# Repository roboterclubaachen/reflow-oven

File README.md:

# reflow-oven

Description: tbd

## Folder structure

#### `pcbs/pcb_name/`
* KiCad files of the PCBs

#### `code/`
* Main Software contains application for an ILI9341 display running via LVGL on modm for easier user control of the reflow oven.

## License

Software is licensed under [GPLv3](LICENSE).
Hardware (PCB files, ...) is licensed under [CERN OHL v.1.2](LICENSE.hardware).

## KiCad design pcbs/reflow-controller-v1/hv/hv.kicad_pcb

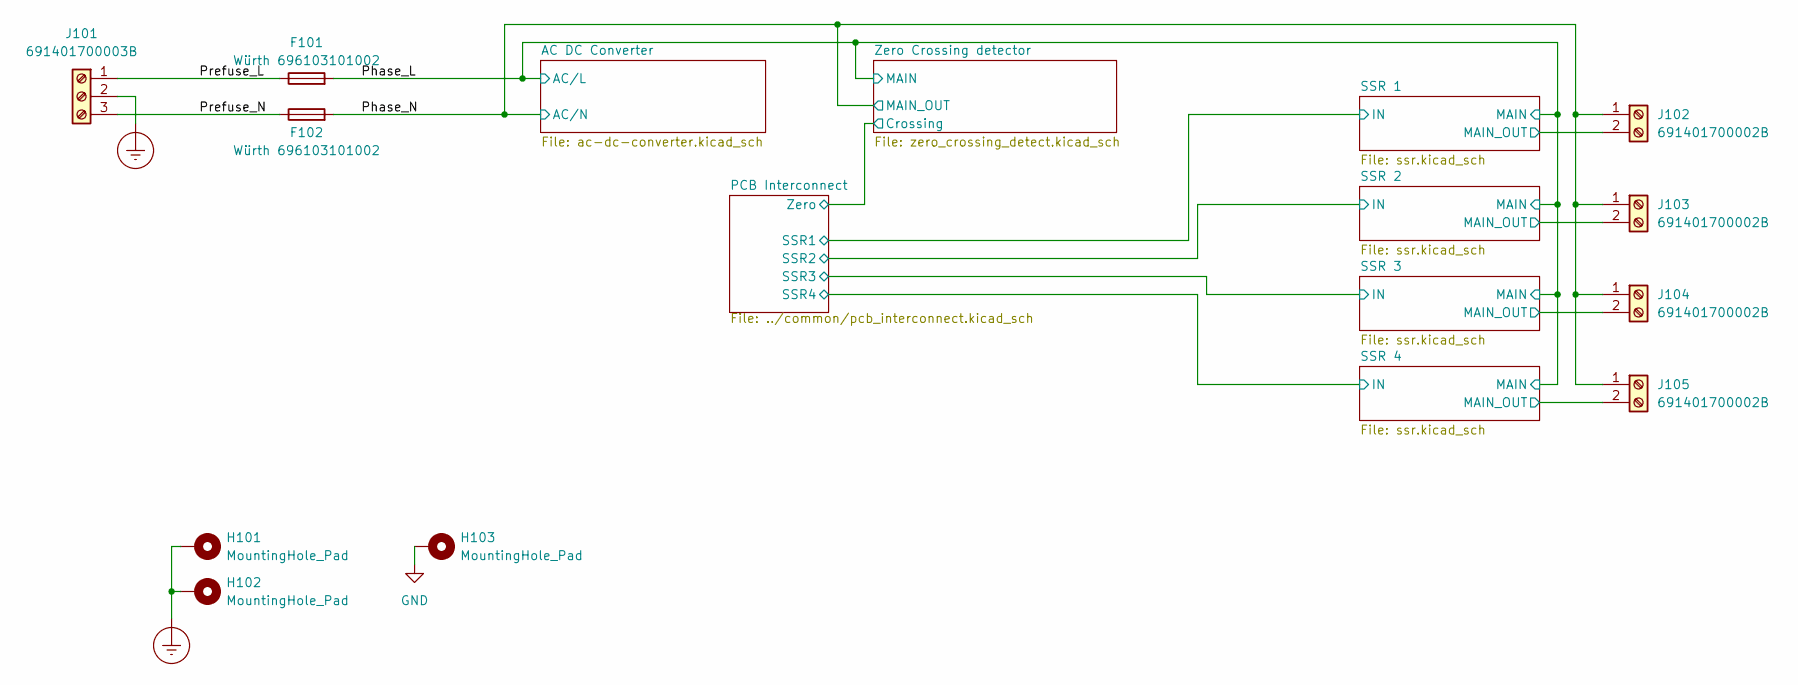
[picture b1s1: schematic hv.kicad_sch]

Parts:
F101, F102: Würth 696103101002; Fuseholder_Cylinder-5x20mm_Wuerth_696103101002-SMD_Horizont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
H101, H102, H103: MountingHole_Pad; Mounting_Wuerth_WA-SMSR-3.2mm_H5.1mm_ReverseMount_9775051960
J101: 691401700003B
J102, J103, J104, J105: 691401700002B

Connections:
/Phase_L: F101.2; also elsewhere on the board
/Phase_N: F102.2, J102.1, J103.1, J104.1, J105.1; also elsewhere on the board
/Prefuse_L: F101.1, J101.1
/Prefuse_N: F102.1, J101.3
/SSR 1/MAIN_OUT: J102.2; also elsewhere on the board
/SSR 2/MAIN_OUT: J103.2; also elsewhere on the board
/SSR 3/MAIN_OUT: J104.2; also elsewhere on the board
/SSR 4/MAIN_OUT: J105.2; also elsewhere on the board
Earth_Protective: H101.1, H102.1, J101.2
GND: H103.1; also elsewhere on the board

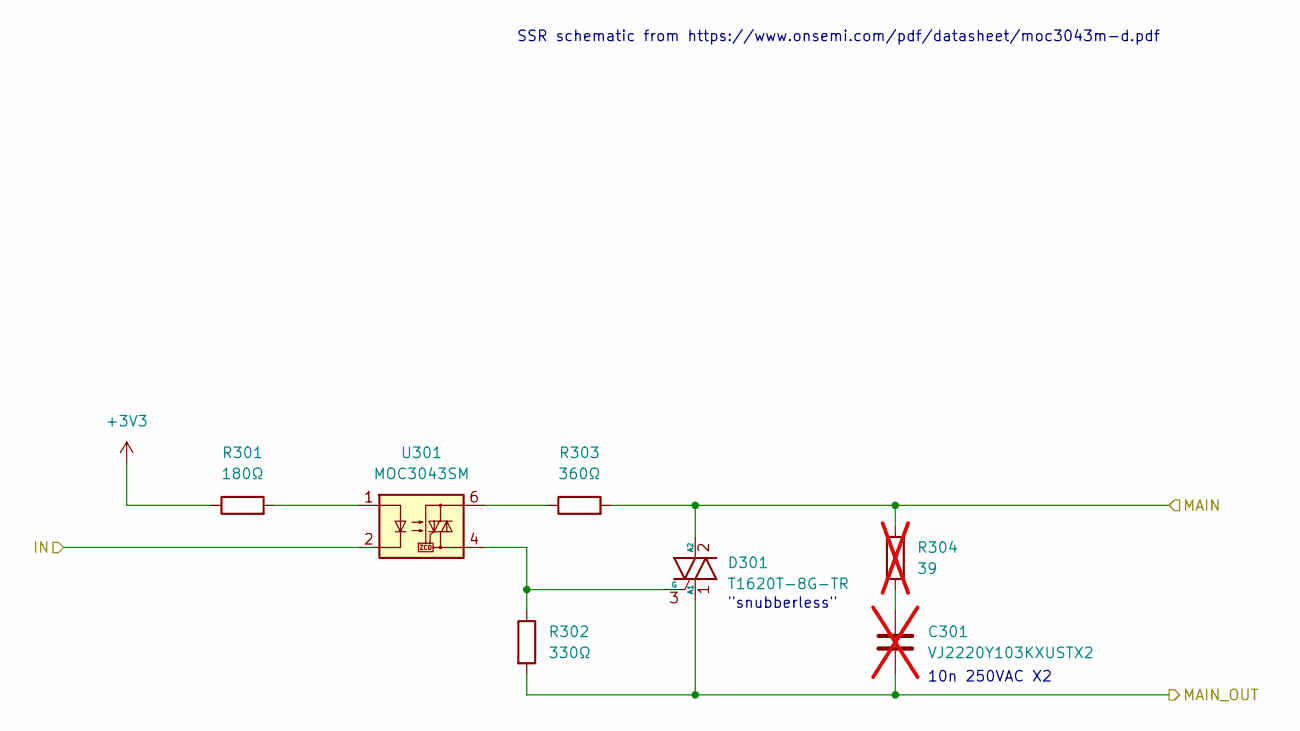
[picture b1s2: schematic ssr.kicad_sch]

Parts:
C301: VJ2220Y103KXUSTX2; C_2220_5750Metric; not fitted
D301: T1620T-8G-TR; TO-263-2
R301: 180Ω; R_0603_1608Metric
R302: 330Ω; R_1206_3216Metric
R303: 360Ω; R_1206_3216Metric
R304: 39; R_1206_3216Metric; not fitted
U301: MOC3043SM; DIP-6_W7.62mm_SMDSocket_SmallPads

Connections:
/PCB Interconnect/SSR1: U301.2; also elsewhere on the board
/Phase_L: D301.2 (A2), R303.2, R304.1; also elsewhere on the board
/SSR 1/MAIN_OUT: C301.2, D301.1 (A1), R302.2; also elsewhere on the board
unnamed: C301.1, R304.2
unnamed: D301.3 (G), R302.1, U301.4
unnamed: R301.2, U301.1
unnamed: R303.1, U301.6

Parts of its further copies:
C401, C501, C601: VJ2220Y103KXUSTX2; C_2220_5750Metric; not fitted
D401, D501, D601: T1620T-8G-TR; TO-263-2
R401, R501, R601: 180Ω; R_0603_1608Metric
R402, R502, R602: 330Ω; R_1206_3216Metric
R403, R503, R603: 360Ω; R_1206_3216Metric
R404, R504, R604: 39; R_1206_3216Metric; not fitted
U401, U501, U601: MOC3043SM; DIP-6_W7.62mm_SMDSocket_SmallPads

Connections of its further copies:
/PCB Interconnect/SSR2: U401.2; also elsewhere on the board
/PCB Interconnect/SSR3: U501.2; also elsewhere on the board
/PCB Interconnect/SSR4: U601.2; also elsewhere on the board
/Phase_L: D401.2 (A2), D501.2 (A2), D601.2 (A2), R403.2, R404.1, R503.2, R504.1, R603.2, R604.1; also elsewhere on the board
/SSR 2/MAIN_OUT: C401.2, D401.1 (A1), R402.2; also elsewhere on the board
/SSR 3/MAIN_OUT: C501.2, D501.1 (A1), R502.2; also elsewhere on the board
/SSR 4/MAIN_OUT: C601.2, D601.1 (A1), R602.2; also elsewhere on the board
unnamed: C401.1, R404.2
unnamed: C501.1, R504.2
unnamed: C601.1, R604.2
unnamed: D401.3 (G), R402.1, U401.4
unnamed: D501.3 (G), R502.1, U501.4
unnamed: D601.3 (G), R602.1, U601.4
unnamed: R401.2, U401.1
unnamed: R403.1, U401.6
unnamed: R501.2, U501.1
unnamed: R503.1, U501.6
unnamed: R601.2, U601.1
unnamed: R603.1, U601.6

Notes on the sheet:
"snubberless"
SSR schematic from https://www.onsemi.com/pdf/datasheet/moc3043m-d.pdf
10n 250VAC X2

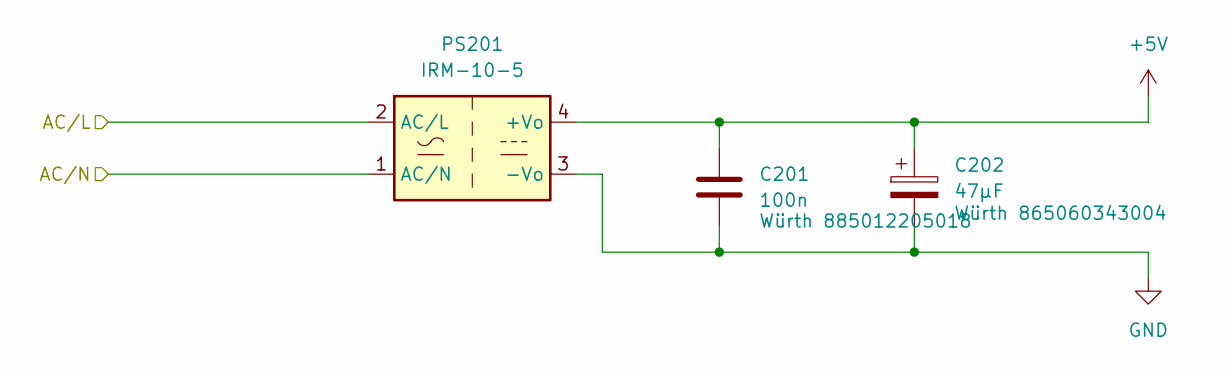
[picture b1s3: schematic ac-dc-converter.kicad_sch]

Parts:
C201: 100n; C_0603_1608Metric
C202: 47μF; CP_Elec_6.3x5.9
PS201: IRM-10-5; Converter_ACDC_MeanWell_IRM-10-xx_THT

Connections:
+5V: C201.1, C202.1, PS201.4 (+Vo); also elsewhere on the board
/Phase_L: PS201.2 (AC/L); also elsewhere on the board
/Phase_N: PS201.1 (AC/N); also elsewhere on the board
GND: C201.2, C202.2, PS201.3 (-Vo); also elsewhere on the board

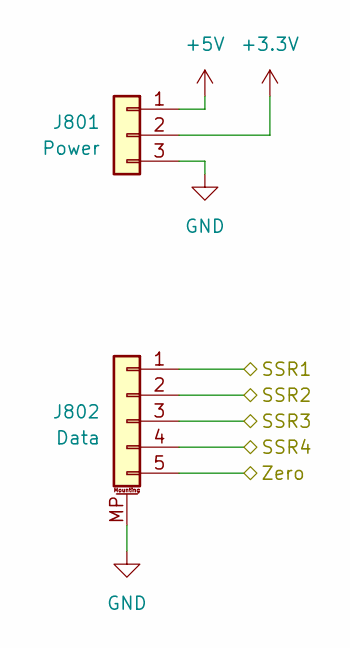
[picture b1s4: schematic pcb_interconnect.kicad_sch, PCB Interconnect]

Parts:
J801: Power; JST_XH_B3B-XH-A_1x03_P2.50mm_Vertical
J802: Data; JST_GH_BM05B-GHS-TBT_1x05-1MP_P1.25mm_Vertical

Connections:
+5V: J801.1; also elsewhere on the board
/PCB Interconnect/SSR1: J802.5; also elsewhere on the board
/PCB Interconnect/SSR2: J802.4; also elsewhere on the board
/PCB Interconnect/SSR3: J802.3; also elsewhere on the board
/PCB Interconnect/SSR4: J802.2; also elsewhere on the board
/PCB Interconnect/Zero: J802.1; also elsewhere on the board
GND: J801.3, J802.MP (MountPin); also elsewhere on the board

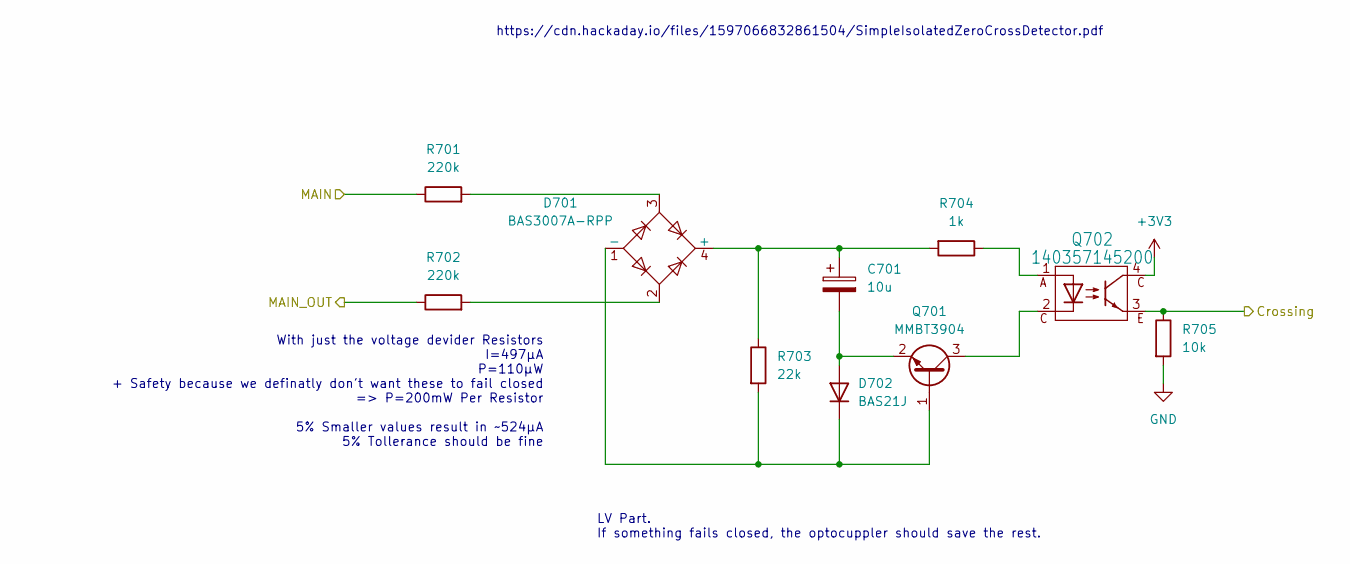
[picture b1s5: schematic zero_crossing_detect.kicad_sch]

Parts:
C701: 10u; CP_Elec_4x5.7
D701: BAS3007A-RPP; SOT-143
D702: BAS21J; D_SOD-323F
Q701: MMBT3904; SOT-23
Q702: 140357145200; WL-OCPT_SOP4
R701, R702: 220k; R_1206_3216Metric
R703: 22k; R_0402_1005Metric
R704: 1k; R_0402_1005Metric
R705: 10k; R_0402_1005Metric

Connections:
/PCB Interconnect/Zero: Q702.3, R705.1; also elsewhere on the board
/Phase_L: R701.1; also elsewhere on the board
/Phase_N: R702.1; also elsewhere on the board
GND: R705.2; also elsewhere on the board
unnamed: C701.1, D701.4 (+), R703.1, R704.2
unnamed: D701.1 (-), D702.1 (K), Q701.1 (B), R703.2
unnamed: D701.2, R702.2
unnamed: D701.3, R701.2
unnamed: C701.2, D702.2 (A), Q701.2 (E)
unnamed: Q701.3 (C), Q702.2
unnamed: Q702.1, R704.1

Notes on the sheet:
https://cdn.hackaday.io/files/1597066832861504/SimpleIsolatedZeroCrossDetector.pdf
LV Part. If something fails closed, the optocuppler should save the rest.
With just the voltage devider Resistors I=497μA P=110μW + Safety because we definatly don't want these to fail closed => P=200mW Per Resistor 5% Smaller values result in ~524μA 5% Tollerance should be fine

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
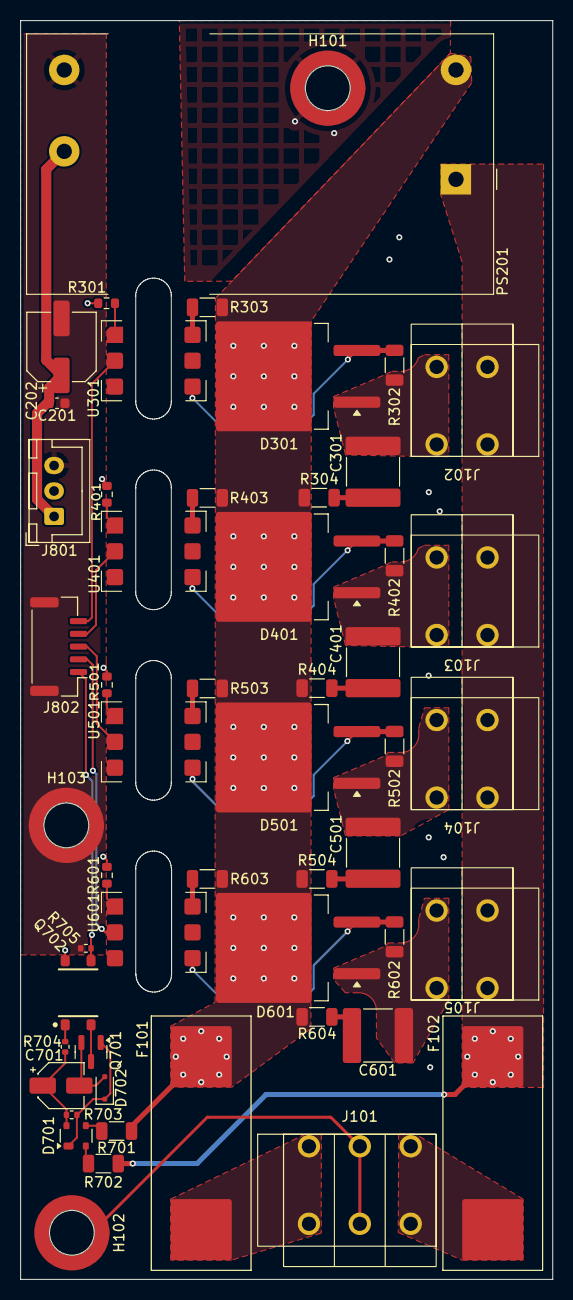
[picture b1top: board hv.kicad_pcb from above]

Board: 4 copper layers, 52.3 x 123.7 mm, 53 parts (0 on the bottom side), 40 nets.

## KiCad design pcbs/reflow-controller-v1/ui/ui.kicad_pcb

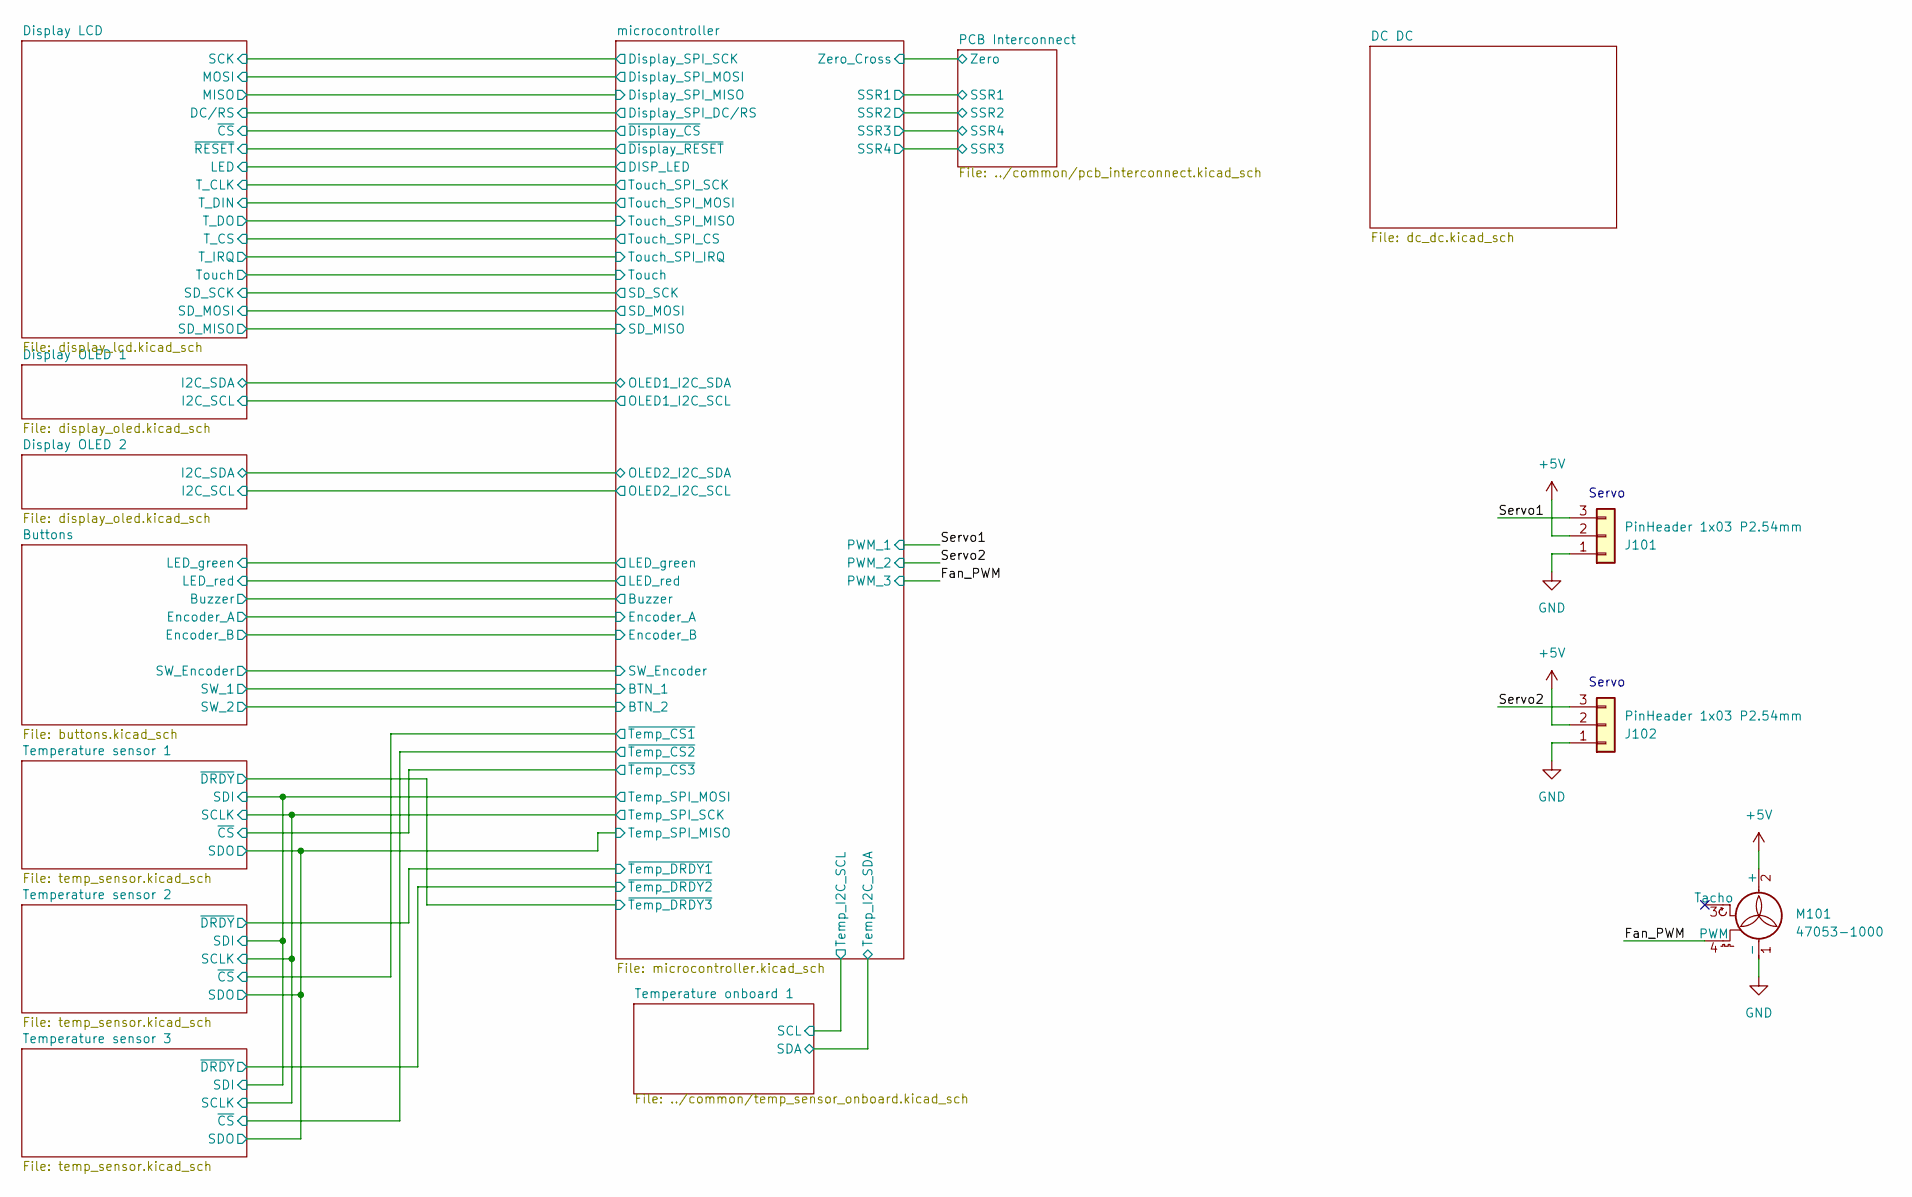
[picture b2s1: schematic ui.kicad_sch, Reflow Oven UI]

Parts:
J101, J102: PinHeader 1x03 P2.54mm; PinHeader_1x03_P2.54mm_Vertical
M101: 47053-1000; Molex_KK-254_AE-6410-04A_1x04_P2.54mm_Vertical

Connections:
+5V: J101.2, J102.2, M101.2 (+); also elsewhere on the board
/Fan_PWM: M101.4 (PWM); also elsewhere on the board
/Servo1: J101.3; also elsewhere on the board
/Servo2: J102.3; also elsewhere on the board

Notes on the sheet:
Servo

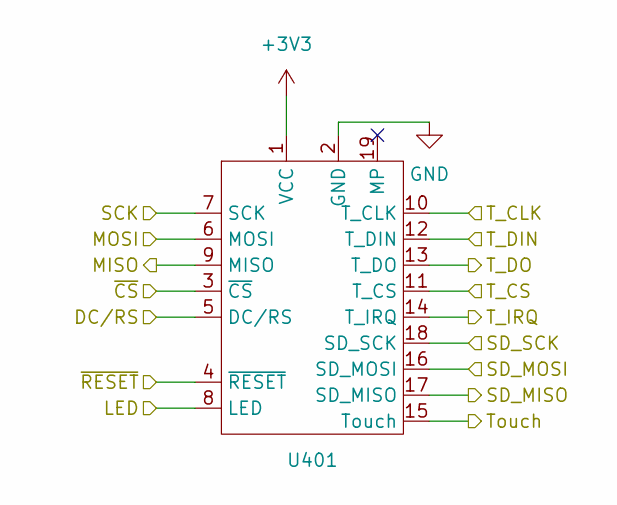
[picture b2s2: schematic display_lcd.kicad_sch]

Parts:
U401: ILI9341 Module

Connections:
+3V3: U401.1 (VCC); also elsewhere on the board
/Display LCD/DC/RS: U401.5 (DC/RS); also elsewhere on the board
/Display LCD/LED: U401.8 (LED); also elsewhere on the board
/Display LCD/MISO: U401.9 (MISO); also elsewhere on the board
/Display LCD/MOSI: U401.6 (MOSI); also elsewhere on the board
/Display LCD/SCK: U401.7 (SCK); also elsewhere on the board
/Display LCD/SD_MISO: U401.17 (SD_MISO); also elsewhere on the board
/Display LCD/SD_MOSI: U401.16 (SD_MOSI); also elsewhere on the board
/Display LCD/SD_SCK: U401.18 (SD_SCK); also elsewhere on the board
/Display LCD/T_CLK: U401.10 (T_CLK); also elsewhere on the board
/Display LCD/T_CS: U401.11 (T_CS); also elsewhere on the board
/Display LCD/T_DIN: U401.12 (T_DIN); also elsewhere on the board
/Display LCD/T_DO: U401.13 (T_DO); also elsewhere on the board
/Display LCD/T_IRQ: U401.14 (T_IRQ); also elsewhere on the board
/Display LCD/Touch: U401.15 (Touch); also elsewhere on the board
/Display LCD/~CS: U401.3 (~CS); also elsewhere on the board
/Display LCD/~RESET: U401.4 (~RESET); also elsewhere on the board

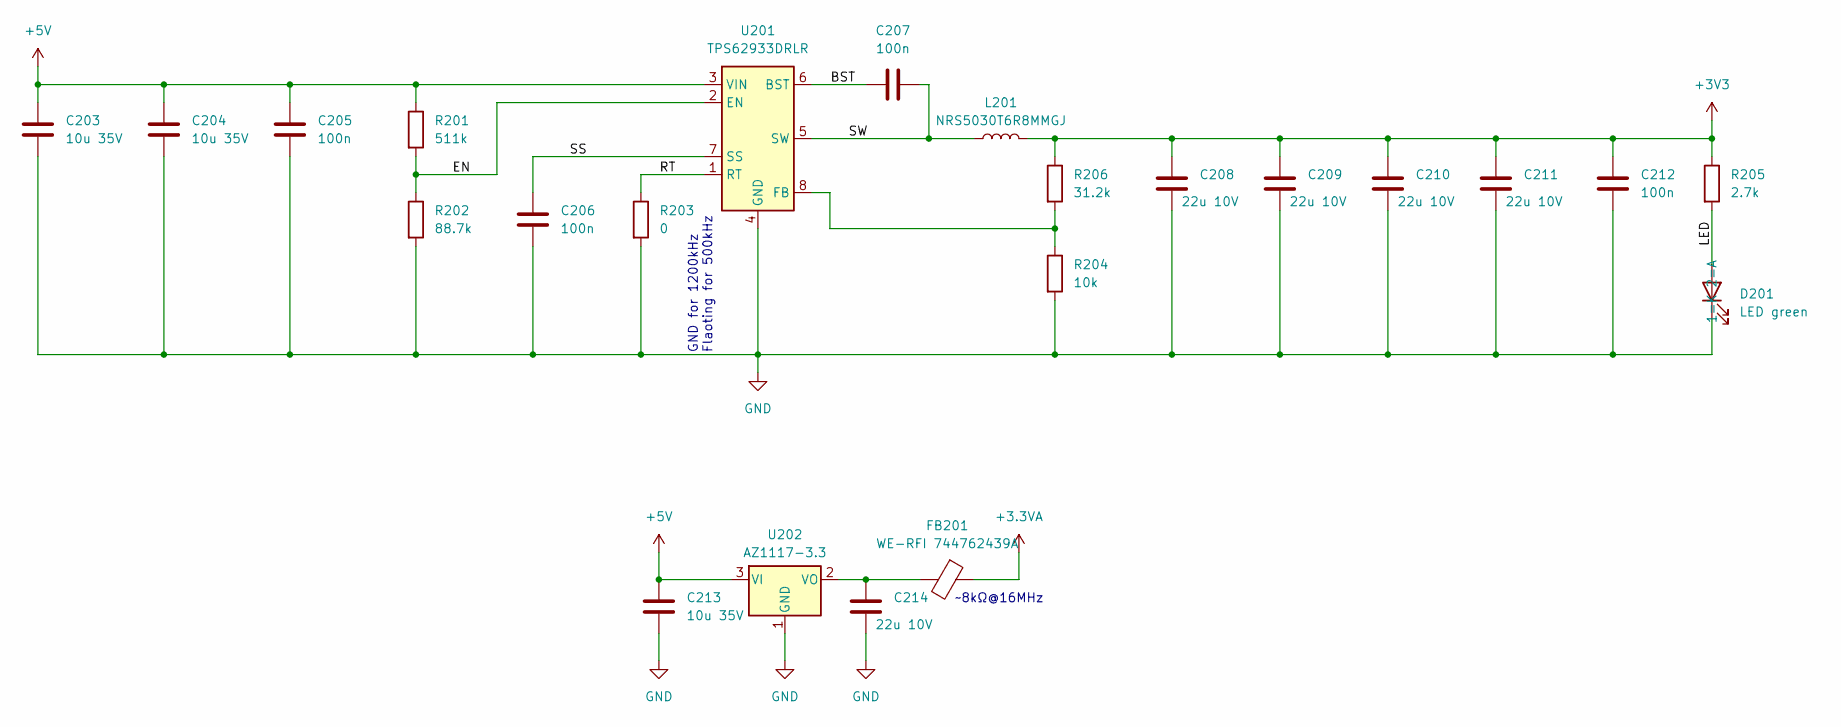
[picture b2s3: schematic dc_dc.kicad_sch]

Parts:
C203, C204, C213: 10u 35V; C_1206_3216Metric
C205, C206, C207, C212: 100n; C_0603_1608Metric
C208, C209, C210, C211, C214: 22u 10V; C_1206_3216Metric
D201: LED green; LED_0603_1608Metric
FB201: WE-RFI 744762439A; L_1008_2520Metric
L201: NRS5030T6R8MMGJ; L_Taiyo-Yuden_NR-50xx
R201: 511k; R_0603_1608Metric
R202: 88.7k; R_0603_1608Metric
R203: 0; R_0603_1608Metric
R204: 10k; R_0603_1608Metric
R205: 2.7k; R_0603_1608Metric
R206: 31.2k; R_0603_1608Metric
U201: TPS62933DRLR; SOT-583-8
U202: AZ1117-3.3; SOT-223-3_TabPin2

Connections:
+3.3VA: FB201.1; also elsewhere on the board
+3V3: C208.1, C209.1, C210.1, C211.1, C212.1, L201.2, R205.1, R206.1; also elsewhere on the board
+5V: C203.1, C204.1, C205.1, C213.1, R201.1, U201.3 (VIN), U202.3 (VI); also elsewhere on the board
/DC DC/BST: C207.1, U201.6 (BST)
/DC DC/EN: R201.2, R202.1, U201.2 (EN)
/DC DC/LED: D201.2 (A), R205.2
/DC DC/RT: R203.1, U201.1 (RT)
/DC DC/SS: C206.1, U201.7 (SS)
/DC DC/SW: C207.2, L201.1, U201.5 (SW)
unnamed: R204.1, R206.2, U201.8 (FB)
unnamed: C214.1, FB201.2, U202.2 (VO)

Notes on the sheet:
~8kΩ@16MHz
GND for 1200kHz Flaoting for 500kHz

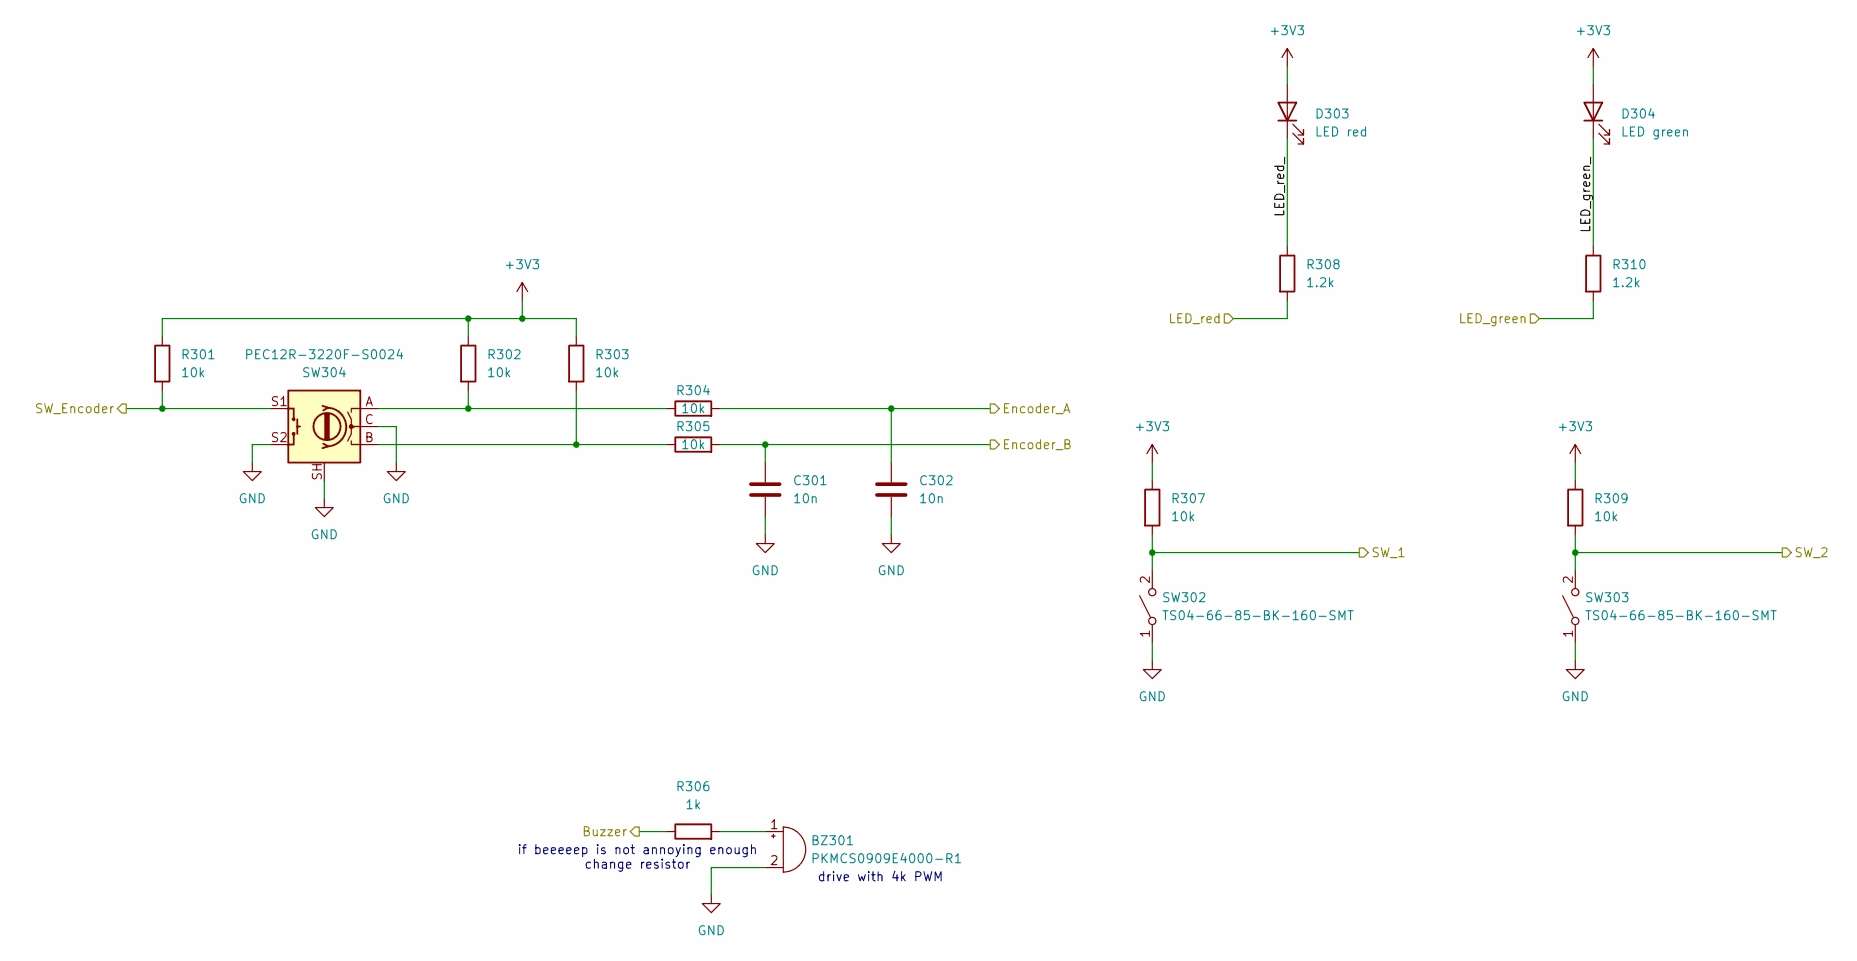
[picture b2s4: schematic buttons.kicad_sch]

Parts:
BZ301: PKMCS0909E4000-R1; Buzzer_Murata_PKMCS0909E
C301, C302: 10n; C_0603_1608Metric
D303: LED red; D_0603_1608Metric
D304: LED green; D_0603_1608Metric
R301, R302, R303, R304, R305, R307, R309: 10k; R_0603_1608Metric
R306: 1k; R_0603_1608Metric
R308, R310: 1.2k; R_0603_1608Metric
SW302, SW303: TS04-66-85-BK-160-SMT; SW_SPST_PTS647_Sx70
SW304: PEC12R-3220F-S0024; RotaryEncoder_Bourns_Vertical_PEC12R-3x17F-Sxxxx

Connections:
+3V3: D303.2 (A), D304.2 (A), R301.1, R302.1, R303.1, R307.1, R309.1; also elsewhere on the board
/Buttons/Buzzer: R306.1; also elsewhere on the board
/Buttons/Encoder_A: C302.1, R304.2; also elsewhere on the board
/Buttons/Encoder_B: C301.1, R305.2; also elsewhere on the board
/Buttons/LED_green: R310.2; also elsewhere on the board
/Buttons/LED_green_: D304.1 (K), R310.1
/Buttons/LED_red: R308.2; also elsewhere on the board
/Buttons/LED_red_: D303.1 (K), R308.1
/Buttons/SW_1: R307.2, SW302.2 (B); also elsewhere on the board
/Buttons/SW_2: R309.2, SW303.2 (B); also elsewhere on the board
/Buttons/SW_Encoder: R301.2, SW304.S1; also elsewhere on the board
unnamed: BZ301.1 (+), R306.2
unnamed: R302.2, R304.1, SW304.A
unnamed: R303.2, R305.1, SW304.B

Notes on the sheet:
if beeeeep is not annoying enough change resistor
drive with 4k PWM

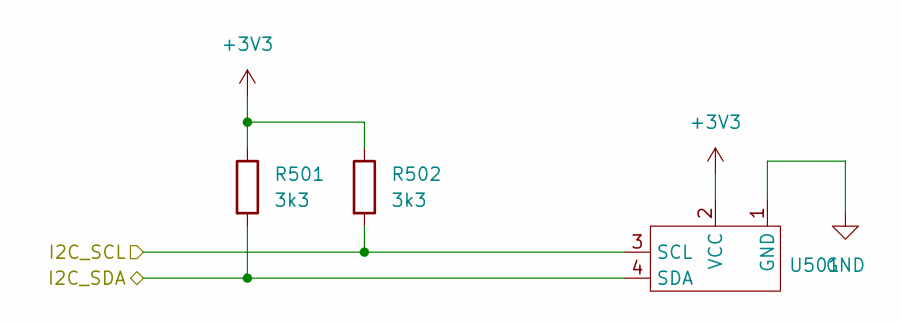
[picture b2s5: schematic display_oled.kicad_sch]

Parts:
R501, R502: 3k3; R_0603_1608Metric
U501: SSD1315 Module

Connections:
+3V3: R501.1, R502.1, U501.2 (VCC); also elsewhere on the board
/Display OLED 1/I2C_SCL: R502.2, U501.3 (SCL); also elsewhere on the board
/Display OLED 1/I2C_SDA: R501.2, U501.4 (SDA); also elsewhere on the board

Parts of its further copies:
R601, R602: 3k3; R_0603_1608Metric
U601: SSD1315 Module

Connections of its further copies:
+3V3: R601.1, R602.1, U601.2 (VCC); also elsewhere on the board
/Display OLED 2/I2C_SCL: R602.2, U601.3 (SCL); also elsewhere on the board
/Display OLED 2/I2C_SDA: R601.2, U601.4 (SDA); also elsewhere on the board

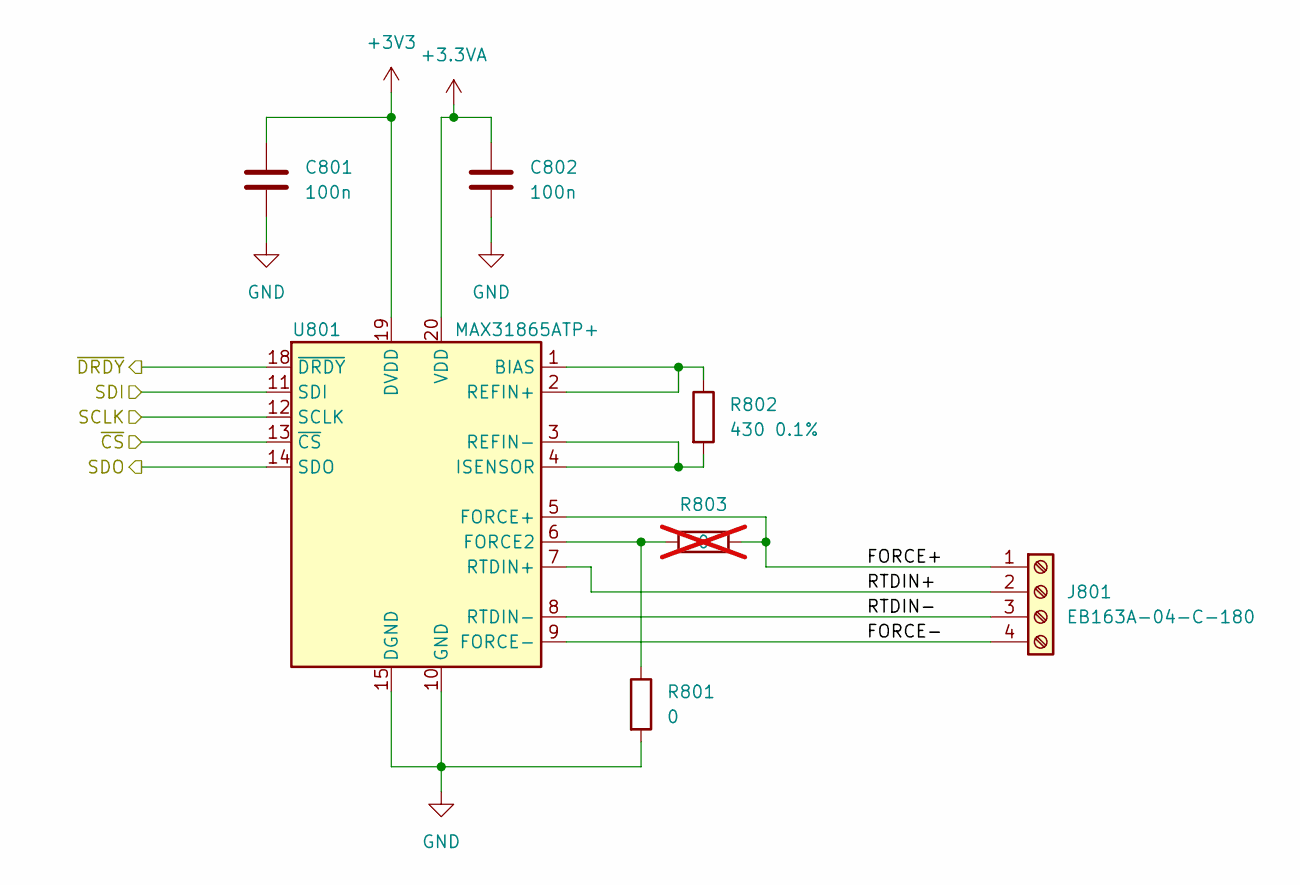
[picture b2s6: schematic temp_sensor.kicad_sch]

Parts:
C801, C802: 100n; C_0603_1608Metric
J801: EB163A-04-C-180; PhoenixContact_SPT_2.5_4-V-5.0-EX_1x04_P5.0mm_Vertical
R801: 0; R_0603_1608Metric
R802: 430 0.1%; R_1206_3216Metric
R803: 0; R_0603_1608Metric; not fitted
U801: MAX31865ATP+; TQFN-20-1EP_5x5mm_P0.65mm_EP3.25x3.25mm

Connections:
+3.3VA: C802.1, U801.20 (VDD); also elsewhere on the board
+3V3: C801.1, U801.19 (DVDD); also elsewhere on the board
/Temperature sensor 1/FORCE+: J801.1, R803.2, U801.5 (FORCE+)
/Temperature sensor 1/FORCE-: J801.4, U801.9 (FORCE-)
/Temperature sensor 1/RTDIN+: J801.2, U801.7 (RTDIN+)
/Temperature sensor 1/SCLK: U801.12 (SCLK); also elsewhere on the board
/Temperature sensor 1/SDI: U801.11 (SDI); also elsewhere on the board
/Temperature sensor 1/SDO: U801.14 (SDO); also elsewhere on the board
/Temperature sensor 1/~CS: U801.13 (~CS); also elsewhere on the board
/Temperature sensor 1/~DRDY: U801.18 (~DRDY); also elsewhere on the board
unnamed: R802.1, U801.1 (BIAS), U801.2 (REFIN+)
unnamed: R801.1, R803.1, U801.6 (FORCE2)
unnamed: R802.2, U801.3 (REFIN-), U801.4 (ISENSOR)

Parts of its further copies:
C901, C902, C1001, C1002: 100n; C_0603_1608Metric
J901, J1001: EB163A-04-C-180; PhoenixContact_SPT_2.5_4-V-5.0-EX_1x04_P5.0mm_Vertical
R901, R1001: 0; R_0603_1608Metric
R902, R1002: 430 0.1%; R_1206_3216Metric
R903, R1003: 0; R_0603_1608Metric; not fitted
U901, U1001: MAX31865ATP+; TQFN-20-1EP_5x5mm_P0.65mm_EP3.25x3.25mm

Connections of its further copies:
+3.3VA: C902.1, C1002.1, U901.20 (VDD), U1001.20 (VDD); also elsewhere on the board
+3V3: C901.1, C1001.1, U901.19 (DVDD), U1001.19 (DVDD); also elsewhere on the board
/Temperature sensor 1/SCLK: U901.12 (SCLK), U1001.12 (SCLK); also elsewhere on the board
/Temperature sensor 1/SDI: U901.11 (SDI), U1001.11 (SDI); also elsewhere on the board
/Temperature sensor 1/SDO: U901.14 (SDO), U1001.14 (SDO); also elsewhere on the board
/Temperature sensor 2/FORCE+: J901.1, R903.2, U901.5 (FORCE+)
/Temperature sensor 2/FORCE-: J901.4, U901.9 (FORCE-)
/Temperature sensor 2/RTDIN+: J901.2, U901.7 (RTDIN+)
/Temperature sensor 2/RTDIN-: J901.3, U901.8 (RTDIN-)
/Temperature sensor 2/~CS: U901.13 (~CS); also elsewhere on the board
/Temperature sensor 2/~DRDY: U901.18 (~DRDY); also elsewhere on the board
/Temperature sensor 3/FORCE+: J1001.1, R1003.2, U1001.5 (FORCE+)
/Temperature sensor 3/FORCE-: J1001.4, U1001.9 (FORCE-)
/Temperature sensor 3/RTDIN+: J1001.2, U1001.7 (RTDIN+)
/Temperature sensor 3/RTDIN-: J1001.3, U1001.8 (RTDIN-)
/Temperature sensor 3/~CS: U1001.13 (~CS); also elsewhere on the board
/Temperature sensor 3/~DRDY: U1001.18 (~DRDY); also elsewhere on the board
unnamed: R902.1, U901.1 (BIAS), U901.2 (REFIN+)
unnamed: R901.1, R903.1, U901.6 (FORCE2)
unnamed: R902.2, U901.3 (REFIN-), U901.4 (ISENSOR)
unnamed: R1002.1, U1001.1 (BIAS), U1001.2 (REFIN+)
unnamed: R1001.1, R1003.1, U1001.6 (FORCE2)
unnamed: R1002.2, U1001.3 (REFIN-), U1001.4 (ISENSOR)
